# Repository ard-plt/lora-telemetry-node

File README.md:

# LoRa Telemetry Node

An end-to-end telemetry link that reads MAVLink 2 data from a Pixhawk over
UART, packs it into a compact binary frame, encrypts it, and relays it over
a long-range 868 MHz LoRa link to a ground station running QGroundControl.

```
[Pixhawk TELEM2] --UART MAVLink2--> [ESP32-S3 TX Node] --LoRa 868MHz--> [ESP32-S3 RX Node] --USB--> [QGroundControl]
```

The ESP32 does not read any sensors itself — Pixhawk is the only data
source. The TX node parses MAVLink, serializes + encrypts a fixed-size
packet, and transmits it over LoRa; the RX node decrypts and re-emits it
as MAVLink 2 over USB so QGroundControl sees a normal telemetry stream.

## LoRa Module

Both nodes use an **EBYTE E22-900T30D** (SX1262, 868 MHz, up to 30 dBm)
LoRa transceiver module, talking to the ESP32 over UART in the module's
Normal (transparent) mode.

| Parameter | Value |
|---|---|
| Frequency | 868.0 MHz |
| Spreading Factor | SF9 |
| Bandwidth | 125 kHz |
| Coding Rate | 4/5 |
| TX Power | 30 dBm |
| Air Data Rate | selectable, 0.3–62.5 kbps (see below) |

**Power warning:** the E22-900T30D draws up to ~500 mA while transmitting.
Do **not** power it from the ESP32's own 3.3 V regulator — use a dedicated
AMS1117-3.3 LDO (1 A rated), with a shared ground between the ESP32 and
the E22.

### Bridge Mode + Air Data Rate

Each node can run in one of two modes, selected (along with the LoRa air
data rate) from a web configuration panel rather than a physical switch:

- **BRIDGE_TRANSPARENT** — the node becomes a transparent UART bridge so
  Mission Planner can reach the Pixhawk directly through the LoRa link for
  parameter/calibration/waypoint work.
- **BRIDGE_COMPRESSED** — normal telemetry mode: TX parses → packs →
  encrypts → transmits; RX receives → decrypts → unpacks → re-emits
  MAVLink.

| Air Rate | UART Baud |
|---|---|
| 0.3 / 1.2 / 2.4 / 4.8 kbps | 9600 |
| 9.6 kbps | 19200 |
| 19.2 kbps | 38400 |
| 38.4 kbps | 57600 |
| 62.5 kbps | 115200 |

Holding the config button (GPIO9) for 3 seconds opens a WPA2-protected
Wi-Fi access point (`TUAV-TX-Config` / `TUAV-RX-Config`) with a captive
portal for selecting bridge mode, air rate, and Wi-Fi password. Changing
the mode/rate from the **RX** node automatically re-synchronizes the
**TX** node over the RF link itself — no need to configure both ends by
hand. See `CLAUDE.md` for the full protocol details.

## PCB

A complete KiCad 10 PCB design lives under [`hardware/pcb/`](hardware/pcb),
covering both nodes as a two-board stack:

- **`main`** — ESP32-S3-DevKitC-1 socket + power section (UBEC input →
  PTC fuse → reverse-polarity protection → a dedicated buck regulator
  that isolates the E22's transmit current pulses from the ESP32 rail).
  Identical design for both TX and RX; fabricate two copies.
- **`tx_rf`** / **`rx_rf`** — the E22-900T30D module plus node-specific
  connectors (TX: Pixhawk TELEM2 JST-GH; RX: SSD1306 OLED header), on a
  small board that plugs directly onto `main` via a 16-pin header/socket
  (`J4`), stacked so the assembly stays compact.

Each project folder includes the schematic, PCB layout, custom footprint/
symbol libraries, and ready-to-fabricate Gerber + drill files
(`gerbers/`). Signal-net routing is left for completion in the KiCad GUI;
net assignments are DRC-verified and the ratsnest will guide it.

| Board | Size |
|---|---|
| `main` | 50 × 71 mm |
| `tx_rf` / `rx_rf` | 50 × 60 mm |

## Hardware Overview

| Component | Model |
|---|---|
| MCU | ESP32-S3-WROOM-1 (via ESP32-S3-DevKitC-1), ×2 |
| LoRa module | EBYTE E22-900T30D (SX1262, 868 MHz, 30 dBm) |
| Pixhawk link | TELEM2 → ESP32 UART2, MAVLink 2, 57600 baud |
| Ground station link | RX node's native USB (USB-OTG), 57600 baud — no FT232 needed |
| OLED (RX only) | SSD1306 128×64, I2C |

## Pin Mapping

### TX Node (air)

| Signal | ESP32 Pin |
|---|---|
| E22 TXD | GPIO4 (UART1 RX) |
| E22 RXD | GPIO5 (UART1 TX) |
| E22 AUX | GPIO6 |
| E22 M0 | GPIO7 |
| E22 M1 | GPIO8 |
| Config button | GPIO9 |
| Pixhawk TELEM2 TX | GPIO16 (UART2 RX) |
| Pixhawk TELEM2 RX | GPIO17 (UART2 TX) |

### RX Node (ground)

| Signal | ESP32 Pin |
|---|---|
| E22 TXD | GPIO4 (UART1 RX) |
| E22 RXD | GPIO5 (UART1 TX) |
| E22 AUX | GPIO6 |
| E22 M0 | GPIO7 |
| E22 M1 | GPIO8 |
| Config button | GPIO9 |
| OLED SDA | GPIO11 |
| OLED SCL | GPIO12 |

E22 M0=LOW, M1=LOW selects Normal TX/RX mode (set automatically at boot).
The E22↔ESP32 UART baud follows the selected air data rate (see table
above); the Pixhawk and ground-station links stay fixed at 57600 baud
regardless of LoRa mode.

## Packet Format (40 bytes, plaintext)

| Offset | Len | Type | Field |
|---|---|---|---|
| 0 | 1 | uint8 | header (fixed 0xAD) |
| 1 | 1 | uint8 | seq_id |
| 2 | 4 | int32 | latitude (degE7) |
| 6 | 4 | int32 | longitude (degE7) |
| 10 | 4 | int32 | altitude_mm (MSL) |
| 14 | 2 | int16 | relative_alt_cm |
| 16 | 2 | int16 | groundspeed_cms |
| 18 | 2 | int16 | airspeed_cms |
| 20 | 2 | int16 | heading_cd |
| 22 | 2 | int16 | roll_cd |
| 24 | 2 | int16 | pitch_cd |
| 26 | 2 | int16 | yaw_cd |
| 28 | 2 | int16 | climb_rate_cms |
| 30 | 2 | uint16 | vbat_mv |
| 32 | 2 | int16 | current_da |
| 34 | 2 | uint16 | lidar_cm (0xFFFF = invalid) |
| 36 | 1 | uint8 | battery_pct |
| 37 | 1 | uint8 | flight_mode |
| 38 | 1 | uint8 | armed |
| 39 | 1 | uint8 | checksum (XOR of bytes 0–38) |

## Encryption

Telemetry is encrypted with AES-128-CTR (ESP32 hardware AES accelerator
via mbedTLS) before transmission: 40-byte plaintext → 40-byte ciphertext,
plus an 8-byte nonce (`seq_id` + low bytes of `millis()`) sent alongside
it. The key lives in `common/aes_config.h` as `AES_KEY` — the checked-in
value is a placeholder, **change it before any real deployment**, and
flash both nodes with the same key.

Separately, copy `common/secrets.h.example` to `common/secrets.h` and
fill in your own `WEB_CONFIG_SALT` (generate one with `openssl rand -hex
32`). This salt authenticates the HMAC on the RX→TX mode/rate sync
command over the RF link; `secrets.h` is gitignored and must never be
committed.

## Build & Flash

```bash
pip install platformio

# TX node
cd tx-node && pio run --target upload

# RX node
cd rx-node && pio run --target upload
```

## QGroundControl Setup

Application Settings → Comm Links → Add:
- Type: **Serial**
- Port: the RX node's COM / `ttyACM` port
- Baud rate: **57600**

See [`docs/qgc_setup.md`](docs/qgc_setup.md) for details and
[`docs/breadboard_wiring.md`](docs/breadboard_wiring.md) for a breadboard
wiring guide (or use the PCB design above instead).

## License

MIT

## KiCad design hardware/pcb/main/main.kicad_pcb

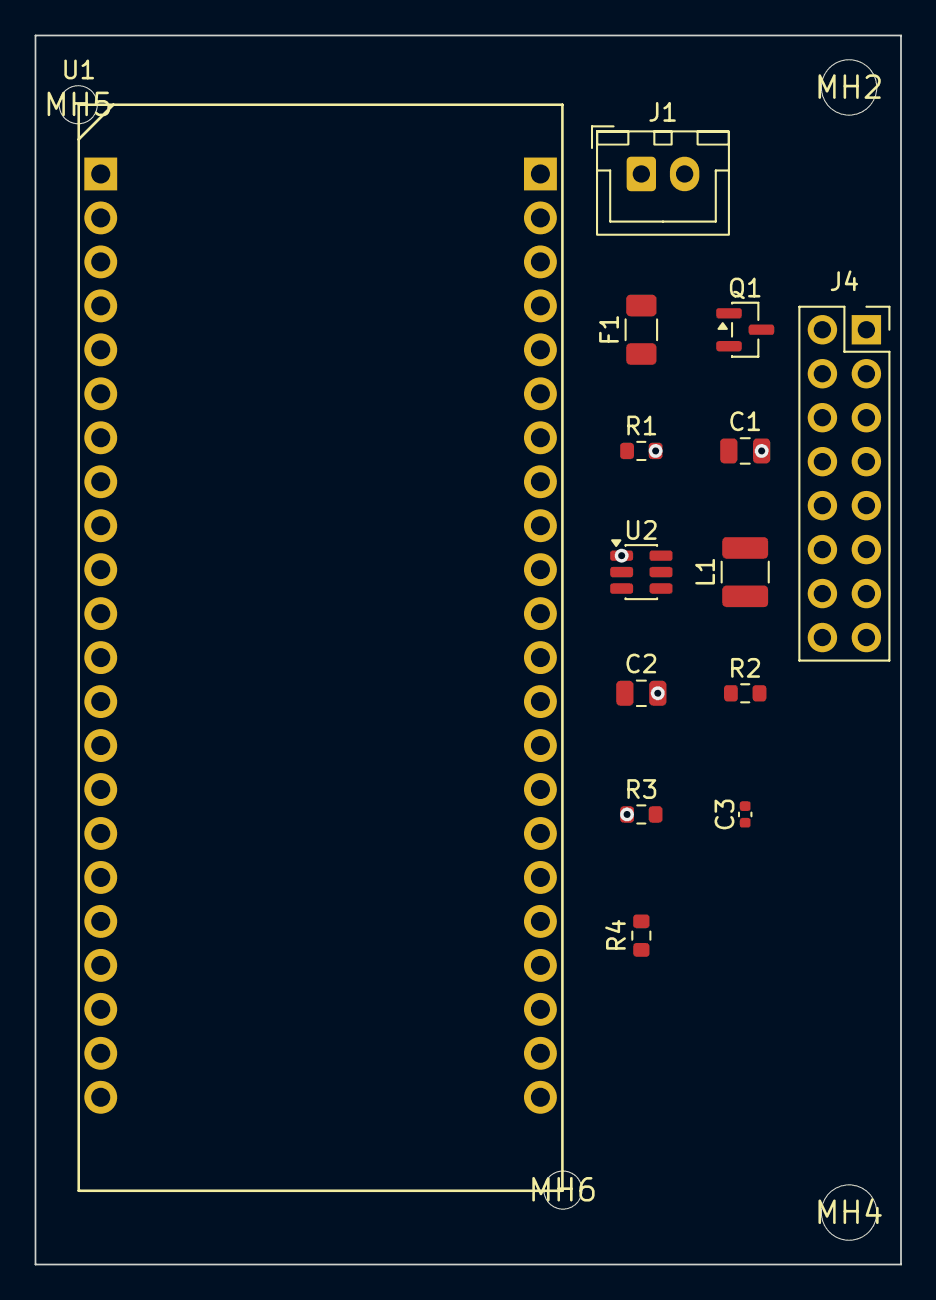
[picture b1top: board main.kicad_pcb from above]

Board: 2 copper layers, 50.0 x 71.0 mm, 18 parts (0 on the bottom side), 22 nets, no tracks yet.

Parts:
C1, C2: 22uF; C_0805_2012Metric
C3: 100nF; C_0402_1005Metric
F1: PTC 1.1A; Fuse_1206_3216Metric
J1: VIN_UBEC; JST_XH_B2B-XH-A_1x02_P2.50mm_Vertical
J4: STACK_TO_RF; PinSocket_2x08_P2.54mm_Vertical
L1: 2.2uH; L_1210_3225Metric
MH2, MH4, MH5, MH6: (no value)
Q1: AO3401A; SOT-23
R1, R3: 10k; R_0603_1608Metric
R2: 56k; R_0603_1608Metric
R4: 100k; R_0603_1608Metric
U1: DevKitC-1; ESP32-S3-DevKitC-1_Socket_2x22_P2.54mm
U2: TPS563201; SOT-23-6

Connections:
+3V3: J4.4, U1.J1-1, U1.J1-2
CONFIG_BTN: J4.10, U1.J1-15
E22_AUX: J4.9, U1.J1-6
E22_M0: J4.7, U1.J1-7
E22_M1: J4.8, U1.J1-12
E22_RXD: J4.6, U1.J1-5
E22_SW: C3.2, L1.1, U2.2
E22_TXD: J4.5, U1.J1-4
E22_VCC: C2.1, J4.3, L1.2, R2.2
GND: C1.2, C2.2, J1.2, J4.1, J4.2, J4.16, R1.2, R3.1, U1.J1-22, U1.J3-1, U1.J3-21, U1.J3-22, U2.1
LED_CTRL: J4.11, U1.J3-5
unnamed: C3.1, U2.6
unnamed: R2.1, R3.2, U2.4
unnamed: R4.1, U2.5
OLED_SCL: J4.15, U1.J1-18
OLED_SDA: J4.14, U1.J1-17
PIXHAWK_RX: J4.13, U1.J1-9
PIXHAWK_TX: J4.12, U1.J1-10
Q1_GATE: Q1.1, R1.1
VIN_FUSED: F1.2, Q1.2
VIN_RAW: F1.1, J1.1
VSYS: C1.1, Q1.3, R4.2, U1.J1-21, U2.3

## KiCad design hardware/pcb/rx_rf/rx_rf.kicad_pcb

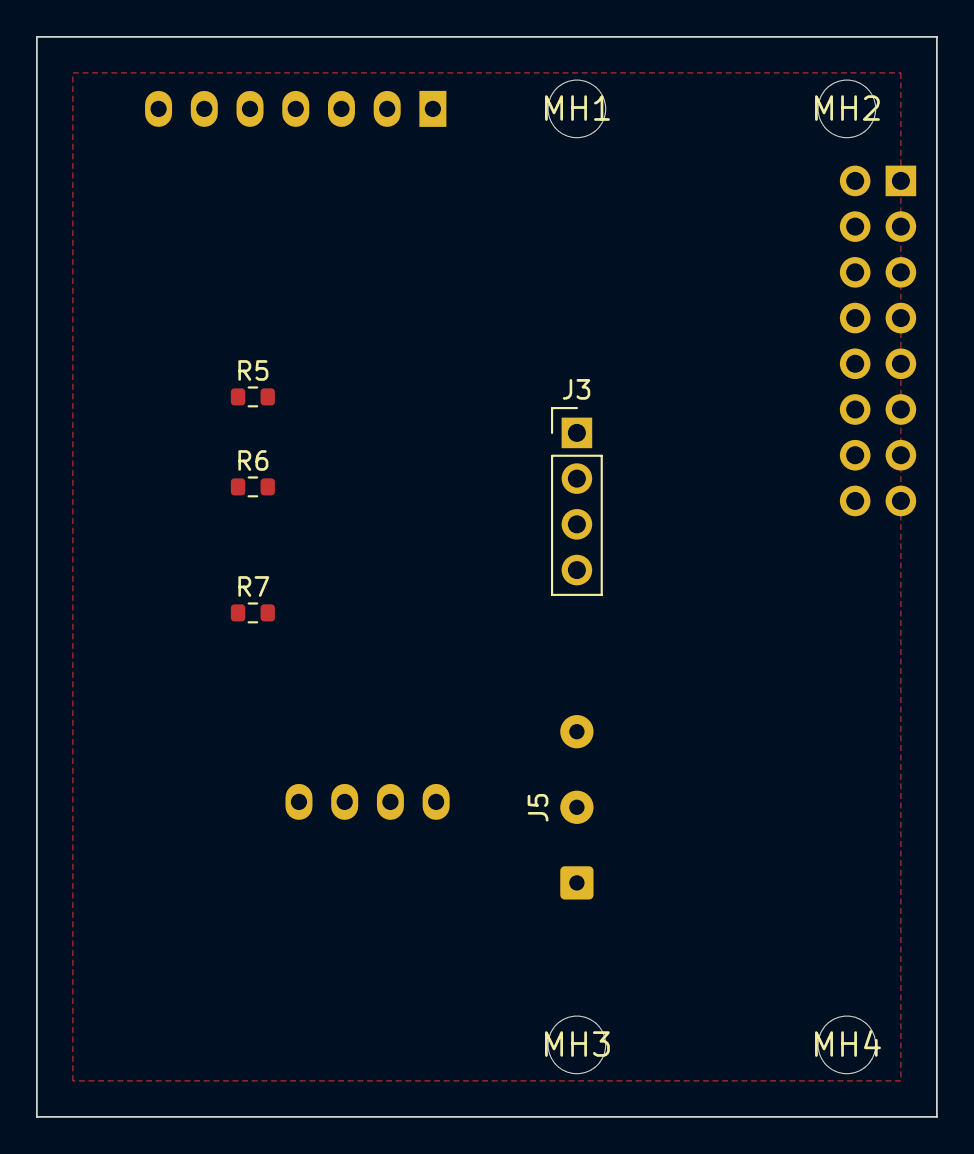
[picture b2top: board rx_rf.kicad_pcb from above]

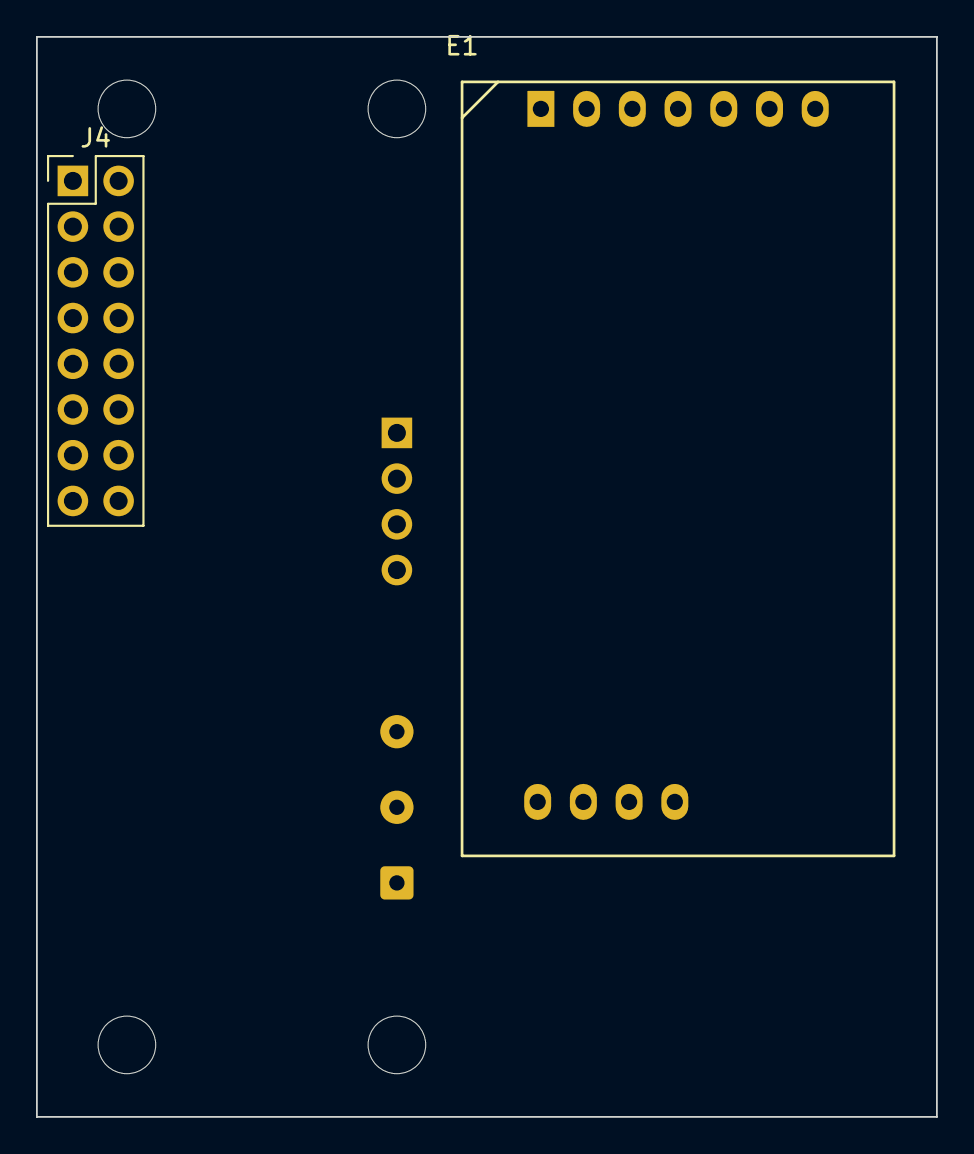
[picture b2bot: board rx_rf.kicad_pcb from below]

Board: 2 copper layers, 50.0 x 60.0 mm, 11 parts (2 on the bottom side), 13 nets, no tracks yet.

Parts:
E1: E22-900T30D
J3: OLED_SSD1306; PinHeader_1x04_P2.54mm_Vertical
J4: STACK_TO_MAIN; PinHeader_2x08_P2.54mm_Vertical
J5: BTN_LED_REMOTE; SolderWire-0.25sqmm_1x03_P4.2mm_D0.65mm_OD1.7mm
MH1, MH2, MH3, MH4: (no value)
R5, R6: 4.7k; R_0603_1608Metric
R7: 330R; R_0603_1608Metric

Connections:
+3V3: J3.1, J4.4, R5.1, R6.1
CONFIG_BTN: J4.10, J5.1
E22_AUX: E1.5, J4.9
E22_M0: E1.1, J4.7
E22_M1: E1.2, J4.8
E22_RXD: E1.3, J4.6
E22_TXD: E1.4, J4.5
E22_VCC: E1.6, J4.3
GND: E1.7, E1.8, E1.9, E1.10, E1.11, J3.2, J4.1, J4.2, J4.16, J5.2
LED_CTRL: J4.11, R7.1
unnamed: J5.3, R7.2
OLED_SCL: J3.4, J4.15, R6.2
OLED_SDA: J3.3, J4.14, R5.2

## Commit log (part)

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2026-05-24 feat: LoRa telemetry node — aşama 1-6 tamamlandı
    TX node: MAVLink2 parse, AES-128-CTR şifreleme, E22 UART LoRa TX (2 Hz)
    RX node: LoRa RX, decrypt, QGroundControl MAVLink çıkışı (57600 baud)
    common: TelemetryPacket (40 byte), AES nonce/IV yardımcıları
    tools: MAVLink simülatörü ve loopback test scriptleri
2026-05-24 chore: CLAUDE.md git takibinden çıkarıldı
2026-05-24 chore: gitignore güncellendi
2026-05-24 docs: geliştirme aşamaları listesi README'den kaldırıldı
